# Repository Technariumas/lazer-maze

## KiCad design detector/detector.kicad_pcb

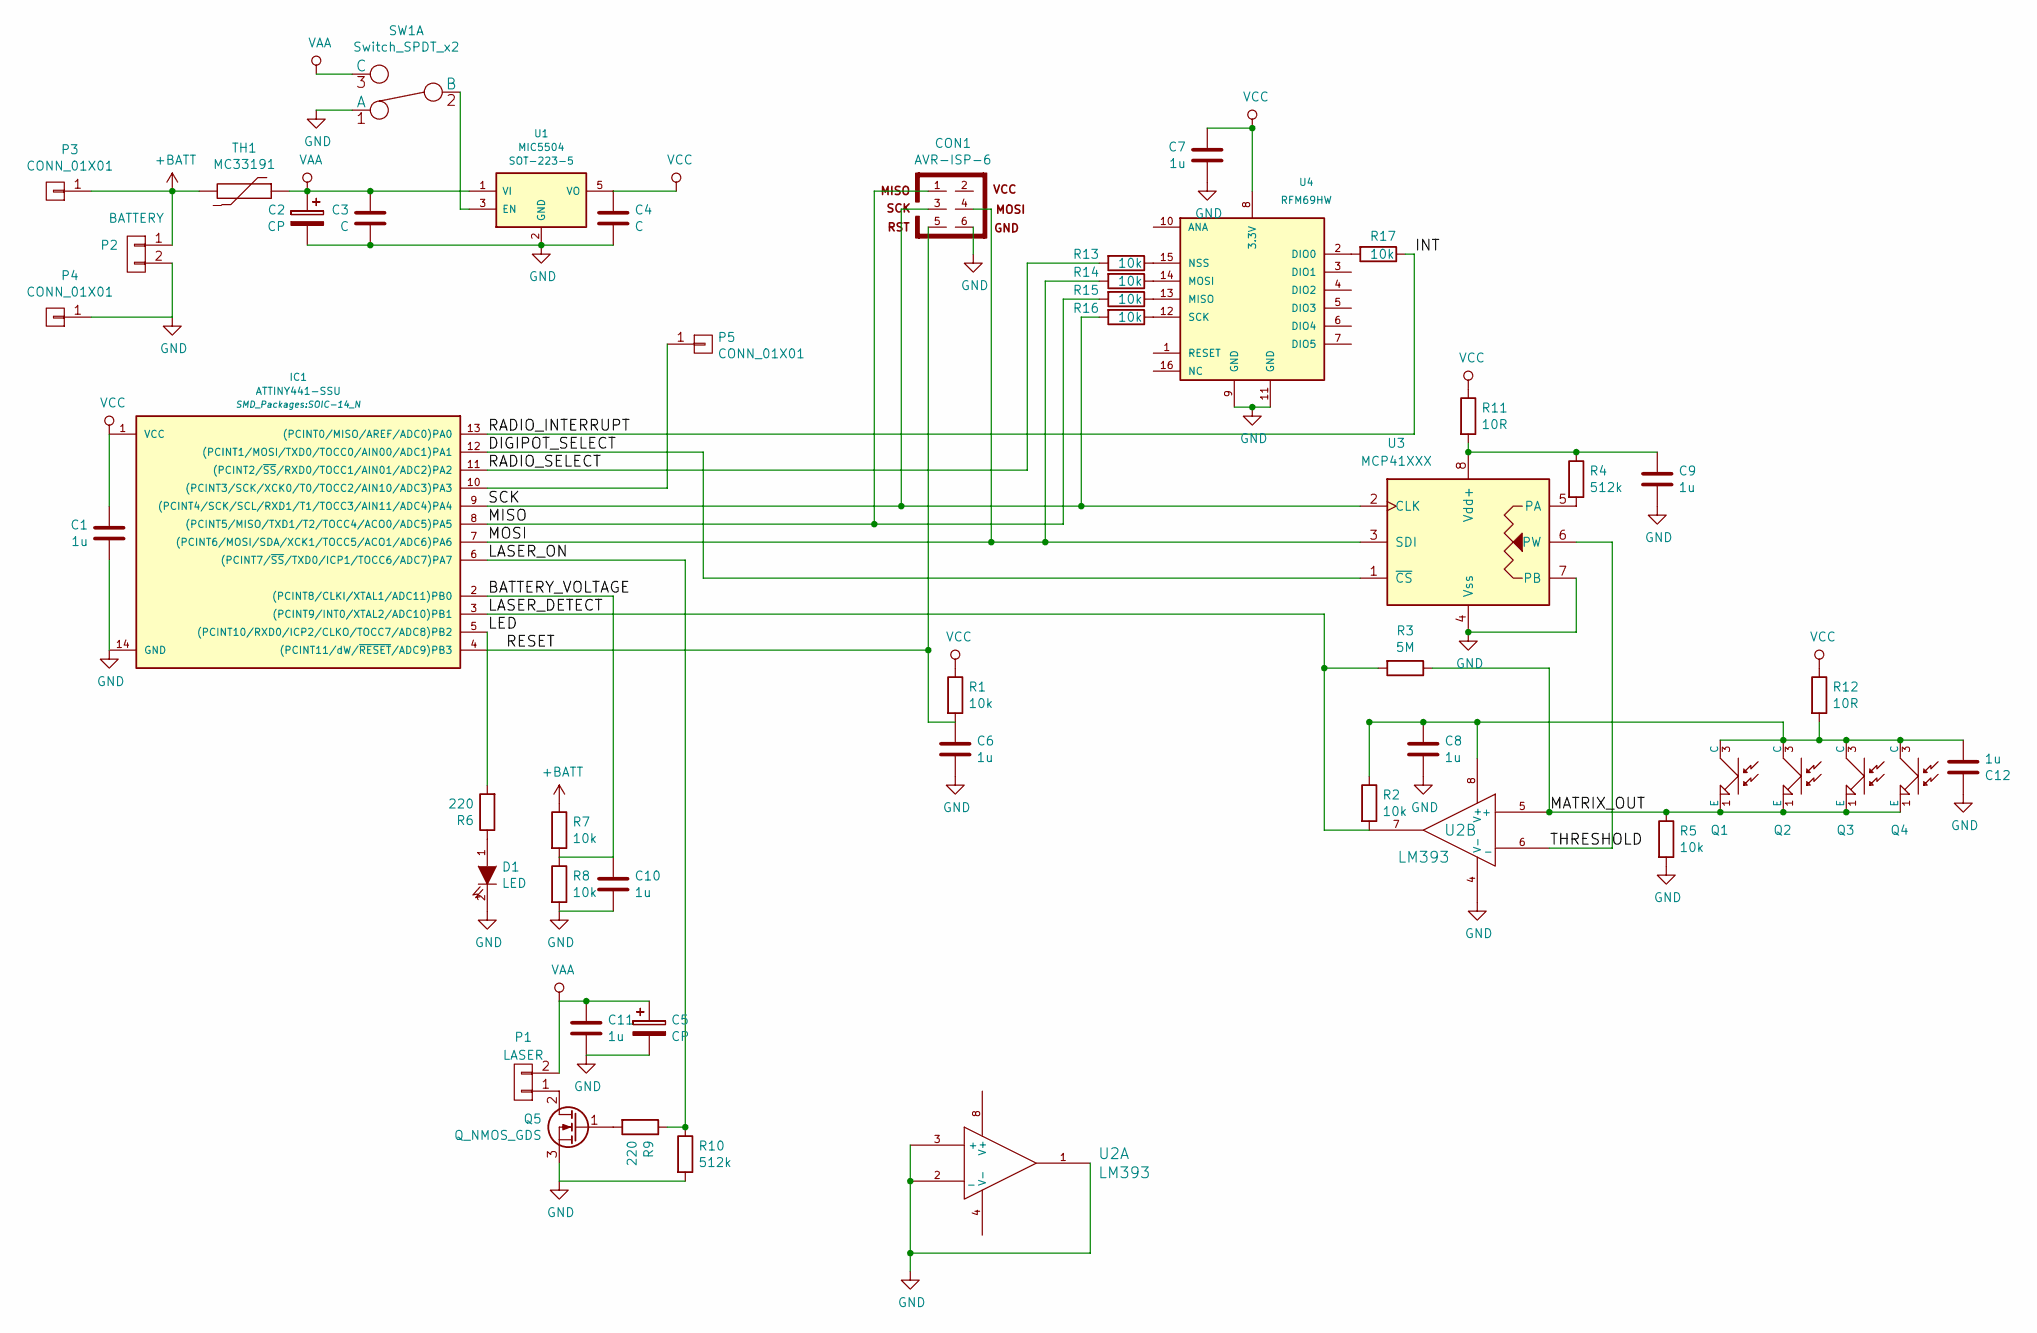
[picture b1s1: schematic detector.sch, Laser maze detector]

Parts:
C1, C6, C7, C8, C9, C10, C11, C12: 1u; C_0603_HandSoldering
C2, C5: CP; c_elec_6.3x5.3; PartNo EDK107M016A9GAA
C3, C4: C; C_0603_HandSoldering
CON1: AVR-ISP-6; Pin_Header_Angled_2x03
D1: LED; Led_0603; PartNo ?
IC1: ATTINY441-SSU; SOIC-14_N; PartNo ?
P1: LASER; Pin_Header_Straight_1x02_Pitch3.96mm_Friction_Lock; PartNo ?
P2: BATTERY; Pin_Header_Straight_1x02_Pitch3.96mm_Friction_Lock; PartNo ?
P3, P4: CONN_01X01; Pin_Header_Straight_1x01; PartNo ?
P5: CONN_01X01; pin_socket_1; PartNo ?
Q1, Q2, Q3, Q4: OPTO_NPN; Led_0805; PartNo ?
Q5: Q_NMOS_GDS; SOT-23_Handsoldering; PartNo FDV303N
R1, R2, R5, R7, R8, R13, R14, R15, R16, R17: 10k; R_0603_HandSoldering
R3: 5M; R_0603_HandSoldering
R4, R10: 512k; R_0603_HandSoldering
R6, R9: 220; R_0603_HandSoldering
R11, R12: 10R; R_0603_HandSoldering
SW1: Switch_SPDT_x2
TH1: MC33191; Fuse_SMD1206_HandSoldering; PartNo MC33191
U1: MIC5504; SOT-223-5; PartNo MIC5504-3.3YM5-TR
U2: LM393; SOIC-8_3.9x4.9mm_Pitch1.27mm; PartNo ?
U3: MCP41XXX; SOIC-8_3.9x4.9mm_Pitch1.27mm; PartNo MCP41100-I/SN
U4: RFM69HW; RFM69HW_SMD_ThroughHole_Handsoldering

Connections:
+BATT: P2.1, P3.1, R7.1, TH1.2
/BATTERY_VOLTAGE: C10.1, IC1.2 ((PCINT8/CLKI/XTAL1/ADC11)PB0), R7.2, R8.1
/DIGIPOT_SELECT: IC1.12 ((PCINT1/MOSI/TXD0/TOCC0/AIN00/ADC1)PA1), U3.1 (~CS~)
/INT: IC1.13 ((PCINT0/MISO/AREF/ADC0)PA0), R17.1
/LASER_DETECT: IC1.3 ((PCINT9/INT0/XTAL2/ADC10)PB1), R2.2, R3.2, U2.7
/LASER_ON: IC1.6 ((PCINT7/~SS~/TXD0/ICP1/TOCC6/ADC7)PA7), R9.1, R10.1
/LED: IC1.5 ((PCINT10/RXD0/ICP2/CLKO/TOCC7/ADC8)PB2), R6.2
/MATRIX_OUT: Q1.1 (E), Q2.1 (E), Q3.1 (E), Q4.1 (E), R3.1, R5.1, U2.5 (+)
/MISO: CON1.1, IC1.8 ((PCINT5/MISO/TXD1/T2/TOCC4/ACO0/ADC5)PA5), R15.2
/MOSI: CON1.4, IC1.7 ((PCINT6/MOSI/SDA/XCK1/TOCC5/ACO1/ADC6)P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), R14.2, U3.3 (SDI)
/RADIO_SELECT: IC1.11 ((PCINT2/~SS~/RXD0/TOCC1/AIN01/ADC2)PA2), R13.2
/RESET: C6.1, CON1.5, IC1.4 ((PCINT11/dW/~RESET~/ADC9)PB3), R1.2
/SCK: CON1.3, IC1.9 ((PCINT4/SCK/SCL/RXD1/T1/TOCC3/AIN11/ADC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), R16.2, U3.2 (CLK)
/THRESHOLD: U2.6 (_), U3.6 (PW)
GND: C1.2, C2.2, C3.2, C4.2, C5.2, C6.2, C7.2, C8.2, C9.2, C10.2, C11.2, C12.1, CON1.6, D1.2 (K), IC1.14 (GND), P2.2, P4.1, Q5.3 (S), R5.2, R8.2, R10.2, SW1.1 (A), U1.2 (GND), U2.1, U2.2 (_), U2.3 (+), U2.4 (V-), U3.4 (Vss), U3.7 (PB), U4.9 (GND), U4.11 (GND); also elsewhere on the board
unnamed: C9.1, R4.1, R11.2, U3.8 (Vdd+)
unnamed: C8.1, C12.2, Q1.3 (C), Q2.3 (C), Q3.3 (C), Q4.3 (C), R2.1, R12.2, U2.8 (V+)
unnamed: D1.1 (A), R6.1
unnamed: IC1.10 ((PCINT3/SCK/XCK0/T0/TOCC2/AIN10/ADC3)PA3), P5.1
unnamed: P1.1, Q5.2 (D)
unnamed: Q5.1 (G), R9.2
unnamed: R4.2, U3.5 (PA)
unnamed: R13.1, U4.15 (NSS)
unnamed: R14.1, U4.14 (MOSI)
unnamed: R15.1, U4.13 (MISO)
unnamed: R16.1, U4.12 (SCK)
unnamed: R17.2, U4.2 (DIO0)
unnamed: SW1.2 (B), U1.3 (EN)
VAA: C2.1, C3.1, C5.1, C11.1, P1.2, SW1.3 (C), TH1.1, U1.1 (VI)
VCC: C1.1, C4.1, C7.1, IC1.1 (VCC), R1.1, R11.1, R12.1, U1.5 (VO), U4.8 (3.3V)

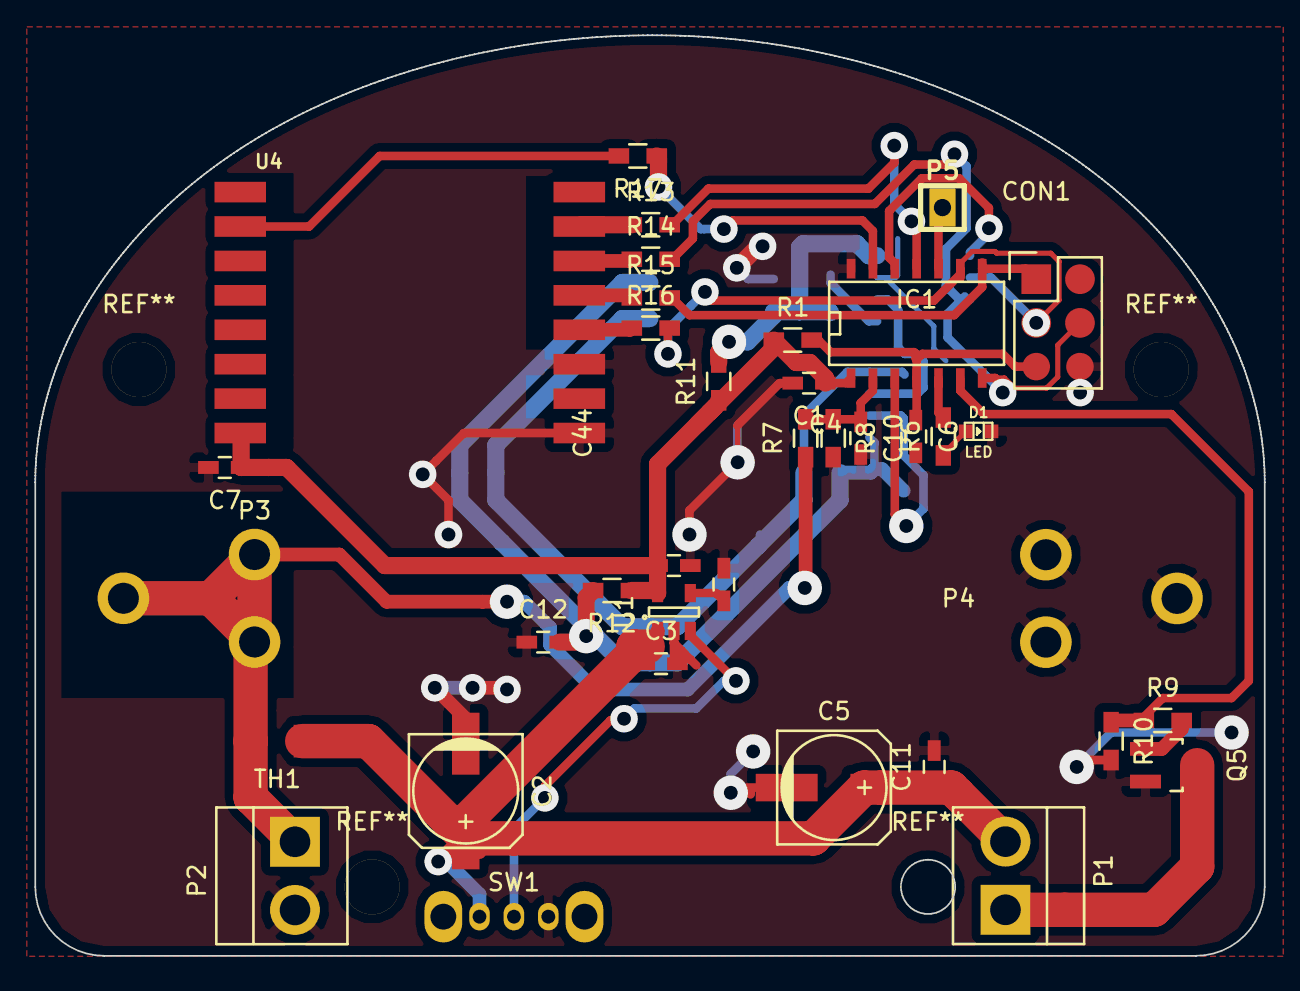
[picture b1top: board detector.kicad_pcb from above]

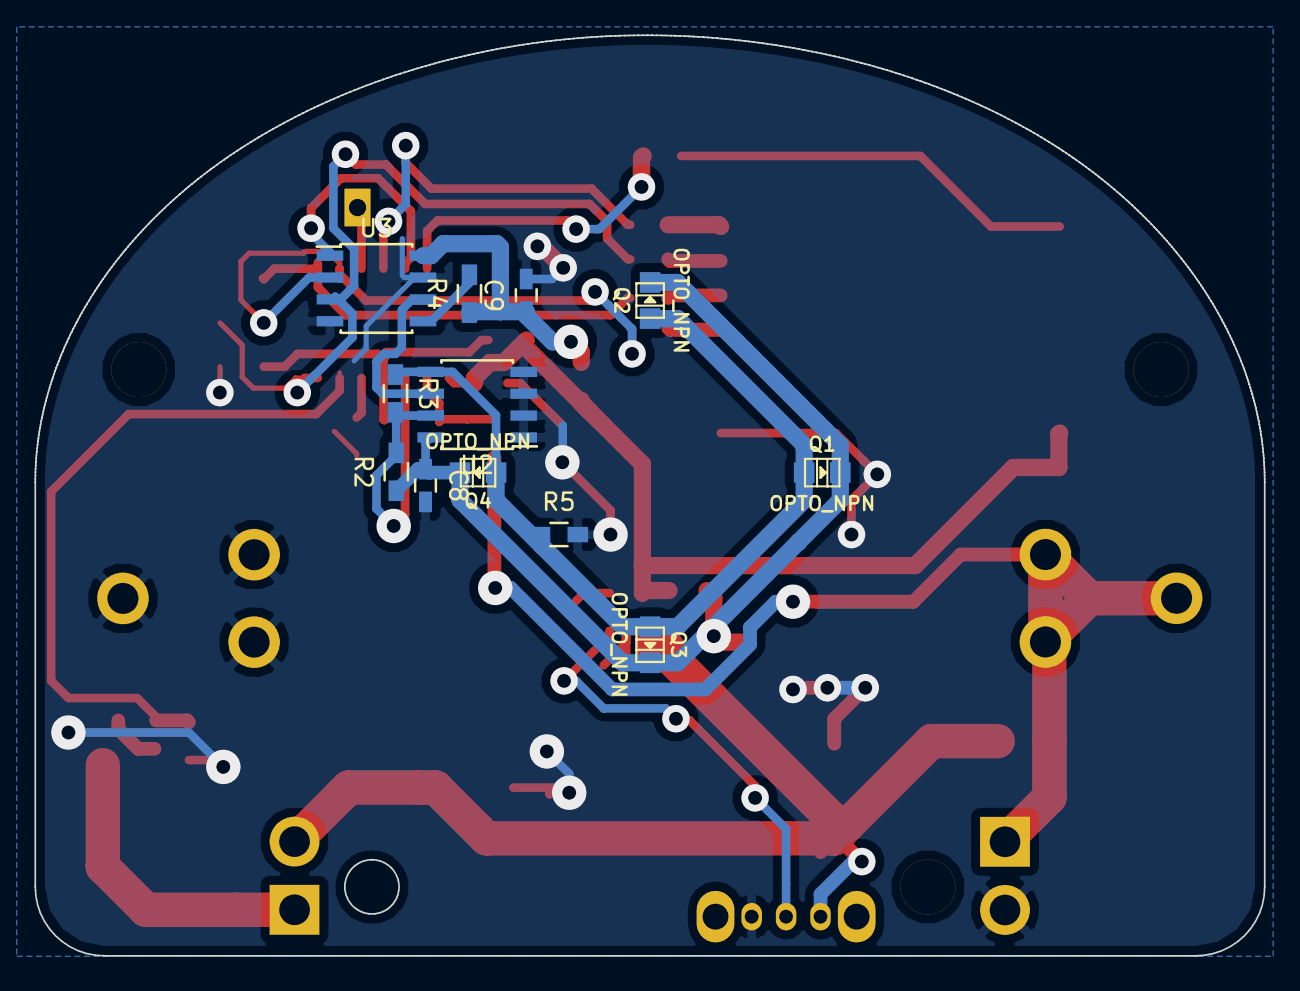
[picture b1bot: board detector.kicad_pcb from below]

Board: 2 copper layers, 71.4 x 53.5 mm, 49 parts (12 on the bottom side), 30 nets.

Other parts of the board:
C44: C; C_0603_HandSoldering

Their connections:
GND: C44.2; also elsewhere on the board

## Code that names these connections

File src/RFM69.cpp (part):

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    /* 0x08 */ { REG_FRFMID, (uint8_t) (freqBand==RF69_315MHZ ? RF_FRFMID_315 : (freqBand==RF69_433MHZ ? RF_FRFMID_433 : (freqBand==RF69_868MHZ ? RF_FRFMID_868 : RF_FRFMID_915))) },
    /* 0x09 */ { REG_FRFLSB, (uint8_t) (freqBand==RF69_315MHZ ? RF_FRFLSB_315 : (freqBand==RF69_433MHZ ? RF_FRFLSB_433 : (freqBand==RF69_868MHZ ? RF_FRFLSB_868 : RF_FRFLSB_915))) },

    // looks like PA1 and PA2 are not implemented on RFM69W, hence the max output power is 13dBm
    // +17dBm and +20dBm are possible on RFM69HW
    // +13dBm formula: Pout = -18 + OutputPower (with PA0 or PA1**)
    // +17dBm formula: Pout = -14 + OutputPower (with PA1 and PA2)**
    // +20dBm formula: Pout = -11 + OutputPower (with PA1 and PA2)** and high power PA settings (section 3.3.7 in datasheet)
    ///* 0x11 */ { REG_PALEVEL, RF_PALEVEL_PA0_ON | RF_PALEVEL_PA1_OFF | RF_PALEVEL_PA2_OFF | RF_PALEVEL_OUTPUTPOWER_11111},
    ///* 0x13 */ { REG_OCP, RF_OCP_ON | RF_OCP_TRIM_95 }, // over current protection (default is 95mA)

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}

ISR(PCINT0_vect) {
	if(PINA & _BV(PA0)) {
		RFM69::isr0();
	}
}

void RFM69::initializeSS() {
	PORTA |= _BV(PA2);
	DDRA |= _BV(PA2);
	PORTA |= _BV(PA2);
	// digitalWrite(_slaveSelectPin, HIGH);
	// pinMode(_slaveSelectPin, OUTPUT);
}

inline void RFM69::ssLow() {
	PORTA &= ~_BV(PA2);
}

inline void RFM69::ssHigh() {
	PORTA |= _BV(PA2);
}

// return the frequency (in Hz)
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// the power configurations are explained in the SX1231H datasheet (Table 10 on p21; RegPaLevel p66): http://www.semtech.com/images/datasheet/sx1231h.pdf
// valid powerLevel parameter values are 0-31 and result in a directly proportional effect on the output/transmission power
// this function implements 2 modes as follows:
//       - for RFM69W the range is from 0-31 [-18dBm to 13dBm] (PA0 only on RFIO pin)
//       - for RFM69HW the range is from 0-31 [5dBm to 20dBm]  (PA1 & PA2 on PA_BOOST pin & high Power PA settings - see section 3.3.7 in datasheet, p22)
void RFM69::setPowerLevel(uint8_t powerLevel)
{
  _powerLevel = (powerLevel > 31 ? 31 : powerLevel);
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}

uint8_t RFM69::getInterruptPinStatus() {
	return (PINA & _BV(PA0)) == _BV(PA0);
}

// internal function - interrupt gets called when a packet is received
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// select the RFM69 transceiver (save SPI settings, set CS low)
void RFM69::select() {
  cli();
  DDRA |= _BV(PA4);
  DDRA |= _BV(PA6);

#if defined (SPCR) && defined (SPSR)
  // save current SPI settings
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  SPSR = _SPSR;
#endif
  sei();
  DDRA &= ~_BV(PA4);
  DDRA &= ~_BV(PA5);
  DDRA &= ~_BV(PA6);
  DDRA &= ~_BV(PA0);

}

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
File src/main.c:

#include <avr/io.h>
#include "SPI.h"
#include "timer.h"
#include <avr/interrupt.h>
#include <avr/eeprom.h>
#include "RFM69.h"

inline static void digipotDeselect() {
	PORTA |= _BV(PA1);
}

inline static void digipotInit() {
	DDRA |= _BV(PA1);
	digipotDeselect();
}

inline static void digipotSelect() {
	PORTA &= ~_BV(PA1);
}

inline static void ledInit() {
	DDRB |= _BV(PB2);
	PORTB &= ~_BV(PB2);
}

inline static void digipotSet(uint8_t b) {
	digipotSelect();
	SPI.transfer(0x11);
	SPI.transfer(b);
	digipotDeselect();
}


inline static void laserOn() {
	PORTA |= _BV(PA7);
}

inline static void laserOff() {
	PORTA &= ~_BV(PA7);
}

inline static void laserInit() {
	DDRA |= _BV(PA7);
	laserOff();
}


inline static void detectorInit() {
	digipotInit();

	//comparator output pin as input
	DDRB &= ~_BV(PB1);

	MCUCR |= _BV(ISC01); //falling edge on INT0
	GIMSK |= _BV(INT0);
	digipotSet(0);

	//aux input with pull up
	DDRA &= ~_BV(PA3);
	PUEA |= _BV(PA3);
}

volatile uint8_t laserTripped = 0;

inline static void detectorArm() {
	laserTripped = 0;
}

uint8_t calibration = 0;

inline static void detectorCalibrate() {

	for(uint8_t b = 0; b < 255; b++) {
		digipotSet(b);
		delay(1);

		if(laserTripped) {
			if(b <= 255 - 10) {
				calibration = b + 10;
			} else {
				calibration = b;
			}
			digipotSet(calibration);
			break;
		}
	}
	detectorArm();
}

inline static uint16_t getBatteryVoltage() {
	ADCSRA |= _BV(ADSC);
	while(ADCSRA & _BV(ADSC)) {
		//wait
	}
	return ADC;
}

inline static void adcInit() {
	ADCSRA = _BV(ADEN) | _BV(ADPS0) | _BV(ADPS1) | _BV(ADPS2);
	DIDR1 = _BV(ADC11D);
	ADMUXA = 11;
	ADMUXB = _BV(REFS1); //internal 2.2 reference
	delay(10);
	getBatteryVoltage();
	delay(10);
	getBatteryVoltage();
}


inline static void ledOn() {
	PORTB |= _BV(PB2);
}

inline static void ledOff() {
	PORTB &= ~_BV(PB2);
}

inline static uint8_t isBatteryLow() {
	return getBatteryVoltage() < 698;
}

inline static void ledRapidBlink(uint8_t times) {
	for(int i = 0; i < times; i++) {
		ledOn();
		delay(200);
		ledOff();
		delay(200);
	}
}

RFM69 radio;

static union {
	char buff[10];
	struct {
		uint8_t nodeId;
		uint8_t messageId;
		uint16_t batteryVoltage;
		uint8_t calibration;
		uint8_t laserTripped;
	} s;
} packet;

#define MESSAGE_STATUS 0
#define MESSAGE_LASER_VISIBLE 1
#define GATEWAY_ADDRESS 254

#define CMD_LASER_ON 1
#define CMD_LASER_OFF 2
#define CMD_CALIBRATE 3
#define CMD_GET_STATUS 4

void sendStatusPacket() {
	packet.s.messageId = MESSAGE_STATUS;
	packet.s.batteryVoltage = getBatteryVoltage();
	packet.s.calibration = calibration;
	packet.s.laserTripped = (0 != (PINB & _BV(PB1)));
	radio.send(GATEWAY_ADDRESS, packet.buff, 9);
}

void sendLaserVisiblePacket() {
	packet.s.messageId = MESSAGE_LASER_VISIBLE;
	packet.s.batteryVoltage = getBatteryVoltage();
	packet.s.calibration = calibration;
	packet.s.laserTripped = (0 != (PINB & _BV(PB1)));
	radio.send(GATEWAY_ADDRESS, packet.buff, 9);
}

#define I2C_ADDRESS_EEPROM_LOCATION (uint8_t*)0x00

inline void waitAndSendStatus() {
	for(uint8_t i = 0; i < packet.s.nodeId; i++) {
		delay(10);
	}
	sendStatusPacket();
}

int main() {
	sei();
	timerInit();

	ledInit();
	ledOn();
	delay(100);
	ledOff();

	packet.s.nodeId = eeprom_read_byte(I2C_ADDRESS_EEPROM_LOCATION);

	SPI.begin();
	laserInit();
	adcInit();

	detectorInit();
	detectorCalibrate();

	uint8_t radioInitialised = radio.initialize(RF69_868MHZ, packet.s.nodeId, 100);
	radio.encrypt(0);
	if(radioInitialised) {
		ledOn();
		delay(1500);
		sendStatusPacket();
		ledOff();
	} else {
		ledRapidBlink(2);
	}
	
	laserOn();

	while(1) {

		if(laserTripped) {
			ledOn();
			sendStatusPacket();
			delay(10);
			while((0 == (PINB & _BV(PB1)))){
				//WAIT
			}
			sendLaserVisiblePacket();
			detectorArm();
			while(0 == (PINA & _BV(PA3))) {
				//WAIT
			}
		} else {
			ledOff();
		}

		if(laserTripped || 0 == (PINA & _BV(PA3))) {
			sendStatusPacket();
			delay(300);
			while(0 == (PINA & _BV(PA3))) {
				//WAIT
			}
			delay(300);
		}


		if(radio.receiveDone()) {
			switch((char)radio.DATA[0]) {
				case CMD_LASER_ON: laserOn(); break;
				case CMD_LASER_OFF: laserOff(); break;
				case CMD_CALIBRATE: detectorCalibrate(); break;
				case CMD_GET_STATUS: waitAndSendStatus(); break;
			}
		}

		if(isBatteryLow()) {
			laserOff();
			radio.sleep();
			while(1) {
				ledRapidBlink(10);
				delay(2000);
			}
		}
	}
}


/*
int main2() {
	sei();
	timerInit();
	SPI.begin();

	ledInit();
	digipotInit();
	laserInit();


	uint8_t b = 0;

	uint8_t radioInitialised = radio.initialize(RF69_868MHZ, 98, 100);
	if(radioInitialised) {
		laserOn();
		delay(1000);
		laserOff();
	} else {
		laserOn();
		delay(200);
		laserOff();
		delay(200);
		laserOn();
		delay(200);
		laserOff();
	}
	radio.encrypt(0);

	while(1) {
		if(PINB & _BV(PINB1)) {
			PORTB |= _BV(PB2);
		} else {
			PORTB &= ~_BV(PB2);
		}
		delay(10);
		digipotSet(b++);
		radio.send(1, buff, 9);
	}
	return 0;
}
*/

ISR(INT0_vect){
	laserTripped = 1;
}

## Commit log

2016-03-04 Initial commit, add the first 3dprints, bom, etc
2016-03-05 Add initial schematics, add simulation of hysteresis
2016-03-05 Add comparator to the BOM
2016-03-11 Add more details, add a chapter on lasers
2016-03-11 Add footprints, prepare for PCB routing
2016-03-11 More specific BOM
2016-03-11 Cleanup and add docu
2016-03-11 Add ebay laser pic
2016-03-14 Add a comparator schematics
2016-03-14 Add rationale about the design change and laser analysis results
2016-03-15 Add case pic
2016-03-15 Fix the pic
2016-03-25 Schematics changes: change RF module to RFM69, add onboard phototransistors, add a switch for laser, put programming header on proper pins, add PTC to the power supply, add voltage measurement divide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
2016-03-25 Label all nets
2016-03-25 Add new 3d files
2016-03-25 Add RFM69W docu
2016-03-25 Add RF module test results
2016-03-25 Add more pics to documentation. Pics are always good
2016-03-25 Play around with github and stl files
2016-03-25 play around more
2016-03-25 Remove junk that does not render
2016-03-26 Source the components, fill the bom, add battery connectors, remove electrolytic from regulator output, put it to the laser
2016-03-26 Change comparator to SO8 package. Add I2C pullups.
2016-03-26 New PCB outline. Add 3D models to PCB. Start routing
2016-03-26 Add a proper symbol for LDO
2016-03-29 Add new outline dxf
2016-03-29 Change digipot to event more expensive but easy to solder SO8 SPI based one
2016-03-29 Put LED to place, connect the laser on line
2016-03-30 The first version of the board sent to manufacturing
2016-03-30 Add pics of pcb render and 3d-printed case
2016-04-06 Add a carcass of the firmware
2016-04-10 Swap comparator inputs so that we could implement MCU wakeup on INT0 low level
2016-04-10 Swap comparator pins on PCB, move R5 so that ground connection is shorter
2016-04-15 REV2 of the board
2016-04-15 Put R3 to the right place - as a hysteresis resistor
2016-04-15 Add connections to the switch on the bottom side
2016-04-17 Add scope screenshots of different regulator load regulation performance
2016-04-17 Fix 3d model paths
2016-04-17 Remove failed 3d export attempt
2016-04-17 Folder rename
2016-04-17 Rename
2016-04-17 Change the LDO to TI one
2016-04-17 Cleanup some code, experiment a bit with make file
2016-04-17 Put files into order
2016-04-17 Add documentation about LDO selection, make shematics A3
2016-04-28 Added files via upload
    lazer module heatsink-case and module press-in tool blueprints, for turning from aluminum, no holder attachment surface yet
2016-05-01 Add final heatsink blueprint
2016-05-18 Add STL files for case
2016-05-25 Preserve eeprom on chip erase
2016-05-25 Add all the functionality at one go: commands to turn on/off the laser, report status, calibration value
2016-05-25 Something has moved, but probably nothing.
2016-06-07 Add a paragraph about laser heatsinks
2016-06-07 Add PCB pictures
2016-06-07 Add laser fixture clamps
2016-06-07 Add the last case pictures
2016-06-07 Add some text about the case design
2016-07-18 Add auxilary input, wait for laser to become visible after trip
2016-07-18 Send also a laser seen message
2016-07-18 Add gateway code

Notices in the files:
src/RFM69.cpp:
Copyright Felix Rusu (2014), felix@lowpowerlab.com
Public License as published by the Free Software
Public License along with this program.
http://www.gnu.org/licenses/gpl-3.0.txt
